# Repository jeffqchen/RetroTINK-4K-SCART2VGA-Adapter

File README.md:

# RetroTINK 4K SCART2VGA Adapter

This is an adapter that converts the SCART IN port on the side of the [RetroTINK 4K](https://www.retrotink.com/product-page/retrotink-4k) to a rear-facing HD-15 VGA port.

This adapter makes it super easy to hook up my [Console VGA Dongle Series](https://github.com/jeffqchen/Console-VGA-Dongle-Series) to the RetroTINK 4K with one single VGA cable. Since my VGA dongles are not RGBHV devices, it makes more sense to leave the real HD-15 port for those that require RGBHV and use the SCART port instead.

This adapter is physically compatible with both the official shell and my own Founders Edition shell, which will be available at a later point.

------

## Signals

### Video

This adapter mainly accepts SCART-compliant RGBS video signal. Sync formats accepted are CSync, Luma or Composite Video.

This adapter can also pass the following formats through the proper pins:
- YPrPb
- RGsB
- CVBS on Pin 20

Please remember to adjust the input options in the Tink4K respectively.

### Audio

This adapter does not have a discrete analog audio input, since I wish to make the design as simple as possible.

If you are using one of my own VGA dongles, audio is already embedded into the VGA cable.

If you wish to run the audio outside the VGA cable, or use your own video connection/cable, simply hook up your audio into other analog/digital audio inputs on the Tink4K, then adjust the audio input override settings in the Tink4K and save the changes as your own profile.

------

## Parts

- PCB. 1.6mm thick - [Gerber File](https://github.com/jeffqchen/RetroTINK-4K-SCART2VGA-Adapter/blob/main/KiCAD/gerber/RT4K_SCART2VGA.zip)
- 3D Printed Shell - [Link](https://github.com/jeffqchen/RetroTINK-4K-SCART2VGA-Adapter/tree/main/3D%20Print)

- VGA Port Slim, Female - [Link](https://github.com/jeffqchen/JeffParts/blob/main/Connectors/HD15/Slim/Female%20PCB/info.md)
- SCART Male Plug, Cable Type - [Link](https://github.com/jeffqchen/JeffParts/blob/main/Connectors/SCART/Male%20Cable/info.md)
  - *Most cheap SCART cables use this type of plug. The height of the plastic part is around 1cm.*
  - *There is a thinner version (5mm) of this plug and this design is incompatible with it.*
- SMD Resistor, imperial 0603 size, 470 Ohm
  - Buy from wherever you feel like (DigiKey, Mouser, Amazon, AliExpress, eBay)
- 2.54mm-pitched Pin Headers 1x2 and jumper

- [2x] M2x16mm screw and hex nut - [Link](https://github.com/jeffqchen/JeffParts/blob/main/Parts/M2%20M3%20Hex%20Screw%20%26%20Nut/info.md)
- [1x] M4x20m screw and hex nut - [Link](https://github.com/jeffqchen/JeffParts/blob/main/Parts/M4%20Hex%20Screw%20%26%20Nut/info.md)

### 3D Print

Print the models in the given vertical orientation. Support is necessary.

### Preparation

The plastic part of the SCART plug has several injection marks that need to be cleaned up with a sharp knife. Otherwise the PCB won't be able to sit flush with the back of the SCART plug.

------

## Assembly

The most interesting part is to fit the SCART plug into the special footprint and solder it in.

Since these plugs are all made slightly differently, you will need some wiggling action to make all the pins go through the board. My advice would be to use a pair of tweezers and wiggle whichever pin that's not compliant. Fit one entire row/side first, then work on the other. Have patience and it will eventually go in. Never force it as you will bend the pins and make it impossible to fit.

Once the pins are all in, make sure the PCB can sit flush to the back of the plug. If there is any gap, the shell won't be able to close. Check if you missed any injection mark and cut it flush.

Then solder in the pin headers. Make sure they are not crooked or they will interfere with the shell.

Then, solder in the 470 Ohm SMD resistor and the VGA port. All ordinary.

The shell was designed with a very tight tolerance for physical strength. Please make sure you are going straight when sliding the PCB assembly into the shell.

Finally, close up the shell with two sets of M2x16mm screws and nuts.

## Attenuation

When the jumper is closed, there is no additional attenuation on the sync line. This works with in-spec SCART signals.

If you are using 5V TTL-level sync from an out-of-spec device, or a VGA switcher box, you will want to leave the jumper open for the safety of the Tink4K. Addition space below is provided to store the loose jumper.

## Installation

To install the adapter to the RetroTINK 4K, simply plug it in from the side, and fasten it in with one M4x20mm screw. This connection is robust enough for daily abuse.

------

## Special Thanks

Mike Chi - The Father of RetroTINK
- [RetroTINK 4K Product Page](https://www.retrotink.com/product-page/retrotink-4k)
- [Official Website](https://www.retrotink.com)
- [Twitter](https://twitter.com/retrotink2)

------

Shield: [![CC BY-SA 4.0][cc-by-sa-shield]][cc-by-sa]

This work is licensed under a
[Creative Commons Attribution-ShareAlike 4.0 International License][cc-by-sa].

[![CC BY-SA 4.0][cc-by-sa-image]][cc-by-sa]

[cc-by-sa]: http://creativecommons.org/licenses/by-sa/4.0/
[cc-by-sa-image]: https://licensebuttons.net/l/by-sa/4.0/88x31.png
[cc-by-sa-shield]: https://img.shields.io/badge/License-CC%20BY--SA%204.0-lightgrey.svg

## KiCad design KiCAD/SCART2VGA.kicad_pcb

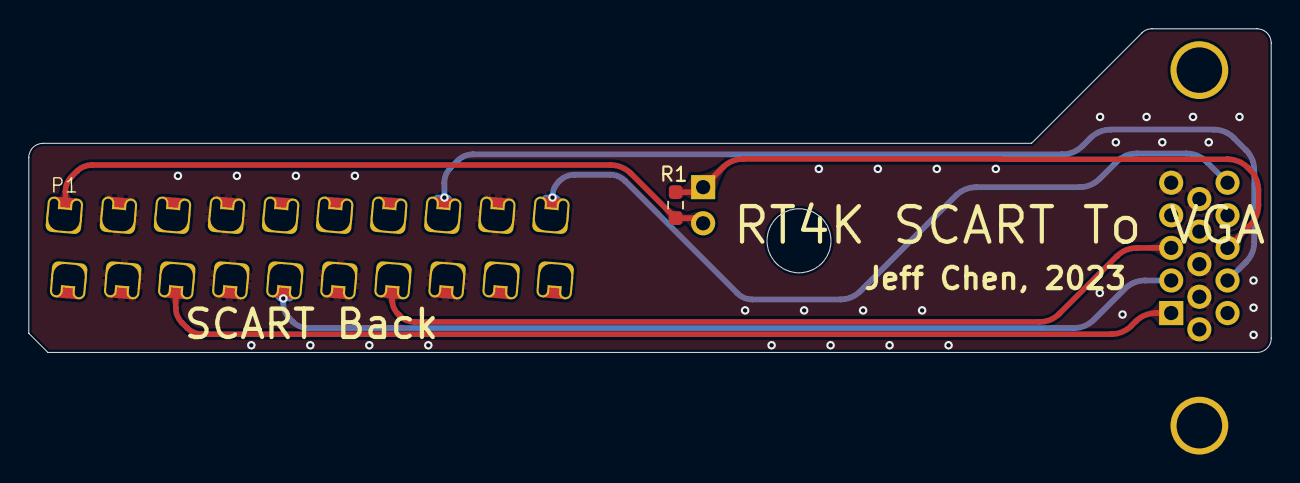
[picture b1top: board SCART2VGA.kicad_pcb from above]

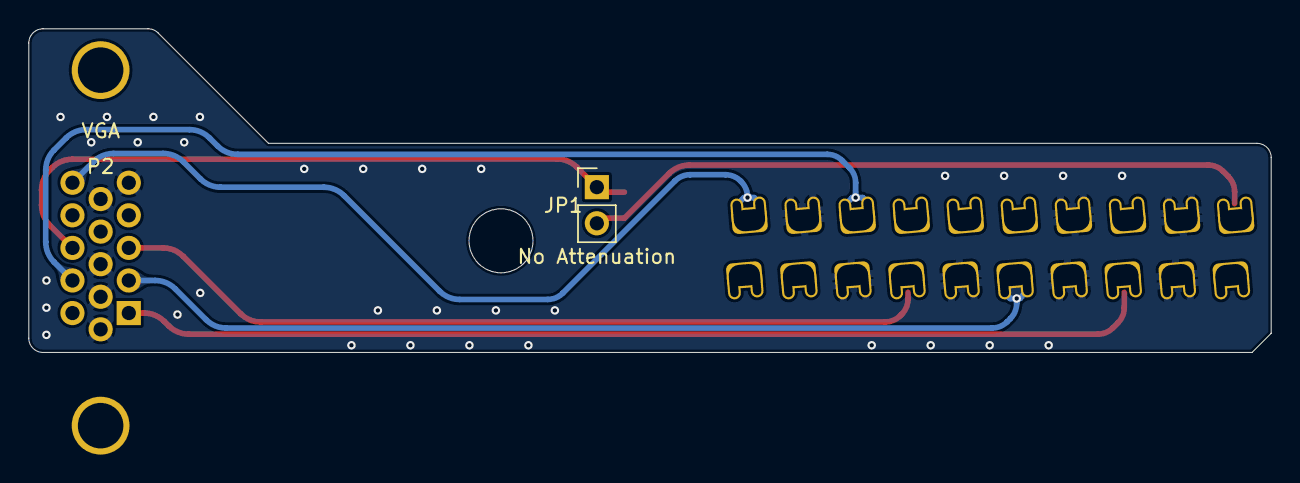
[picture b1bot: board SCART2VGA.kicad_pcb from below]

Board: 2 copper layers, 87.3 x 22.8 mm, 4 parts (2 on the bottom side), 8 nets.

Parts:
JP1: No Attenuation; PinHeader_1x02_P2.54mm_Vertical
P1: SCART_PAL; SCART_THT
P2: VGA; VGA_female_rightangle_slim
R1: 470; R_0603_1608Metric_Pad0.98x0.95mm_HandSolder

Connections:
/Audio_L: P1.6 (Audio_L_In), P2.12 (ID1/SDA)
/Audio_R: P1.2 (Audio_R_In), P2.15 (ID3/SCL)
/Blue: P1.7 (Blue), P2.3 (Blue)
/Green: P1.11 (Green), P2.2 (Green)
/Red: P1.15 (Red), P2.1 (Red)
/Sync: JP1.1 (A), P2.13 (HSYNC), R1.1
/Sync_Processed: JP1.2 (B), P1.20 (CVBS_In), R1.2
GND: P1.4 (Audio_GND), P1.5 (Blue_GND), P1.9 (Green_GND), P1.13 (Red_GND), P1.14 (D2B_GND), P1.17 (CVBS_Out_GND), P1.18 (CVBS_In_GND), P2.5 (HSYNC_GND), P2.6 (Red_GND), P2.7 (Green_GND), P2.8 (Blue_GND), P2.10 (VSYNC_GND)

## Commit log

2023-12-07 Create new
2023-12-07 Initial Upload
2023-12-08 Pics and readme update
2023-12-08 Update license
